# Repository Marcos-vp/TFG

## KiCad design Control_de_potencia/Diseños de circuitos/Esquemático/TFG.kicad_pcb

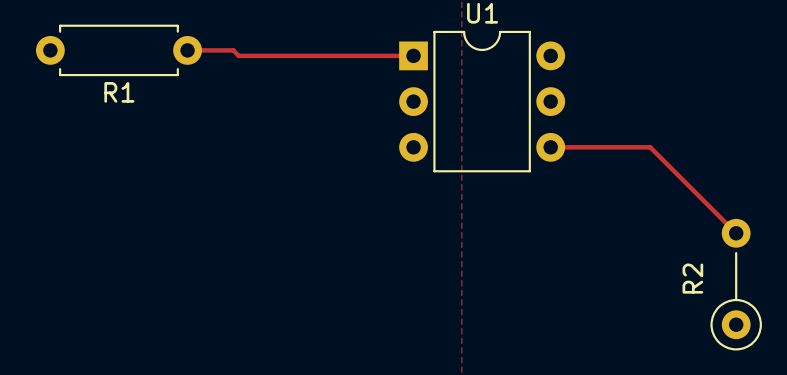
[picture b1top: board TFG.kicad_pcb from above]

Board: 2 copper layers, 3 parts (0 on the bottom side), 2 nets.

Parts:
R1: 1K; R_Axial_DIN0207_L6.3mm_D2.5mm_P7.62mm_Horizontal
R2: 10K; R_Axial_DIN0207_L6.3mm_D2.5mm_P5.08mm_Vertical
U1: 4N35; DIP-6_W7.62mm

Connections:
+5V: R2.2, U1.4, U1.5
unnamed: R1.1, U1.1

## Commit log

2018-09-13 partes
2018-09-14 Add gitignore
2018-09-18 carpeta modificada y actualizada
2019-06-30 actualización estado TFG
2019-06-30 word tfg
